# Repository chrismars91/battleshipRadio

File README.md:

https://www.instructables.com/BattLedRadio-the-LED-Radio-Battleship-SAMD21-Editi/

*** New board gerber below with better JTAG programming pads and a battery powered option. Updated BOM in the link. ***
https://www.pcbway.com/project/shareproject/rfm69_battleship_battery_7544f334.html

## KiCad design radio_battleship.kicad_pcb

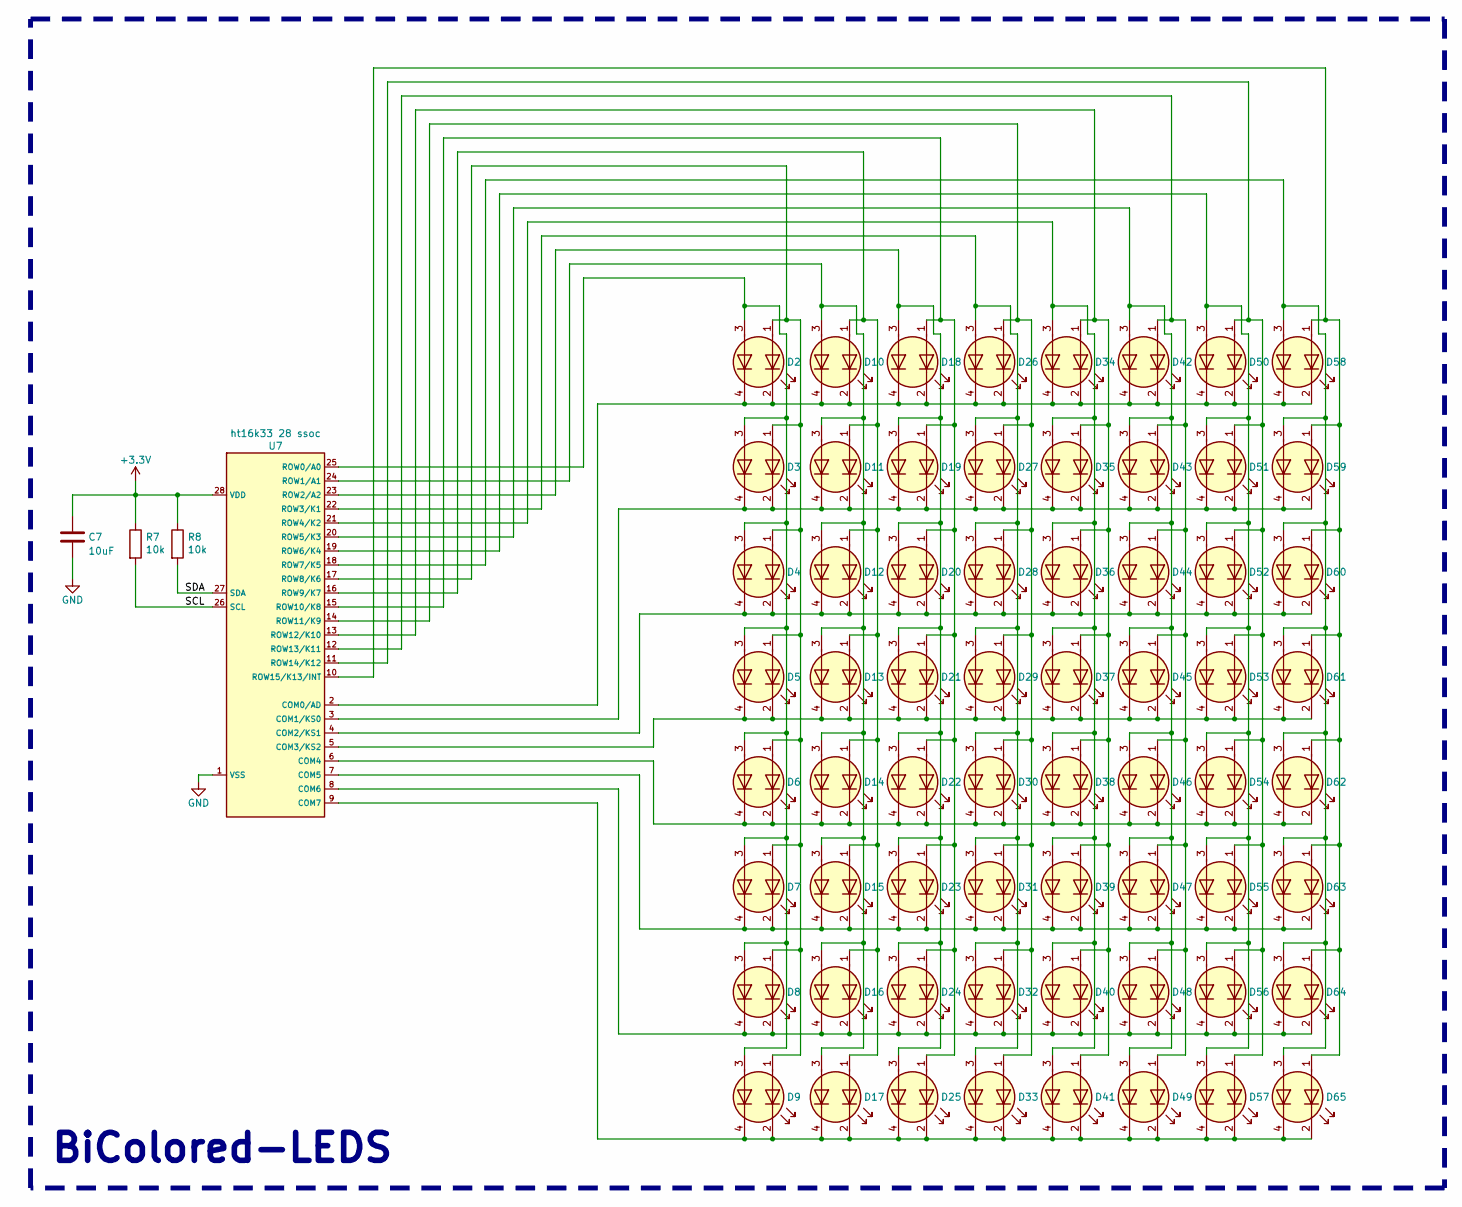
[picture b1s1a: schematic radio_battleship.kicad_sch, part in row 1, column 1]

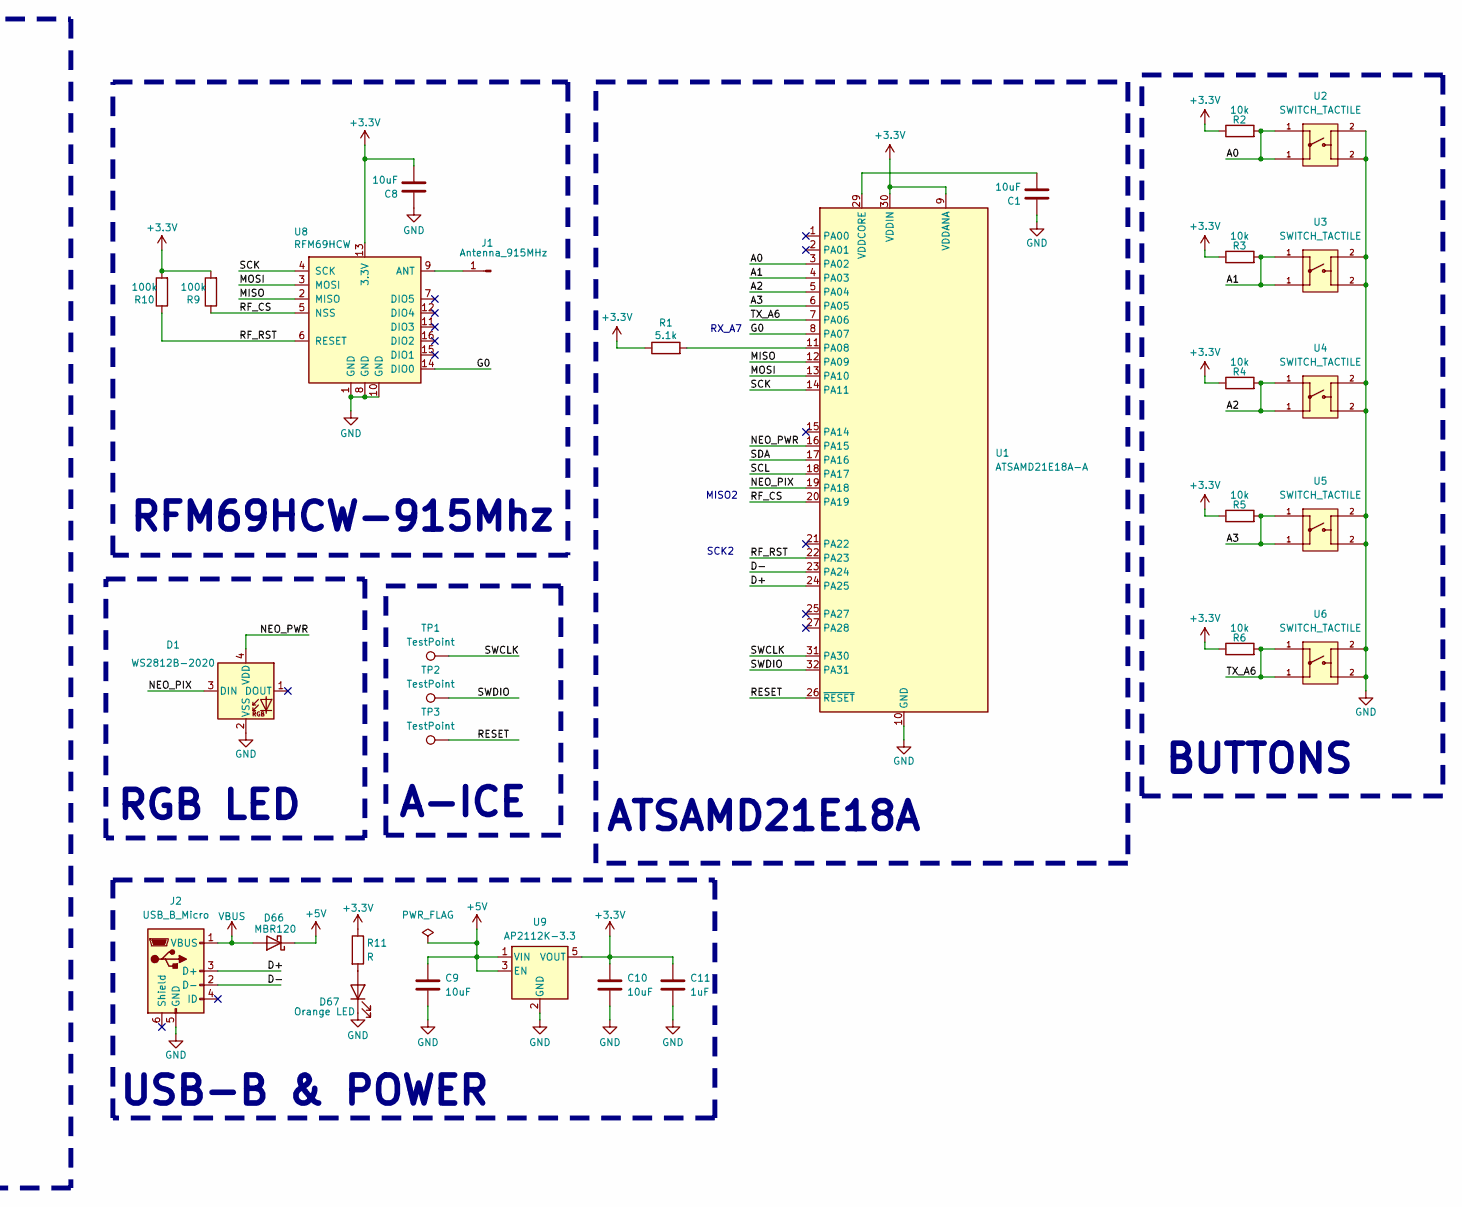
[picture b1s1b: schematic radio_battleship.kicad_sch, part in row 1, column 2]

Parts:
C1, C7, C8, C9, C10: 10uF; C_0603_1608Metric
C11: 1uF; C_0603_1608Metric
D1: WS2812B-2020; custom_ws28_2m_led
D2, D3, D4, D5, D6, D7, D8, D9, D10, D11, D12, D13, D14, D15, D16, D17, D18, D19, D20, D21, D22, D23, D24, D25, D26, D27, D28, D29, D30, D31, D32, D33, D34, D35, D36, D37, D38, D39, D40, D41, D42, D43, D44, D45, D46, D47, D48, D49, D50, D51, D52, D53, D54, D55, D56, D57, D58, D59, D60, D61, D62, D63, D64, D65: LTST-BILED-15X16
D66: MBR120; D_SOD-123F
D67: Orange LED; LED_0805_2012Metric
J1: Antenna_915MHz; ant
J2: USB_B_Micro; USB_Micro-B_Wuerth_629105150521
R1: 5.1k; R_0603_1608Metric
R2, R3, R4, R5, R6, R7, R8: 10k; R_0603_1608Metric
R9, R10: 100k; R_0603_1608Metric
R11: R; R_0603_1608Metric
TP1, TP2, TP3: TestPoint; TestPoint_Pad_2.5x2.5mm
U1: ATSAMD21E18A-A; TQFP-32_7x7mm_P0.8mm
U2, U3, U4, U5, U6: SWITCH_TACTILE
U7: ht16k33 28 ssoc; HT16K33_ssop
U8: RFM69HCW
U9: AP2112K-3.3; SOT-23-5

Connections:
+3.3V: C7.1, C8.2, C10.1, C11.1, R1.1, R2.1, R3.1, R4.1, R5.1, R6.1, R7.1, R8.1, R9.2, R10.2, R11.1, U1.9 (VDDANA), U1.30 (VDDIN), U7.28 (VDD), U8.13 (3.3V), U9.5 (VOUT)
+5V: C9.1, D66.1 (K), U9.1 (VIN), U9.3 (EN)
/A0: R2.2, U1.3 (PA02), U2.1
/A1: R3.2, U1.4 (PA03), U3.1
/A2: R4.2, U1.5 (PA04), U4.1
/A3: R5.2, U1.6 (PA05), U5.1
/D+: J2.3 (D+), U1.24 (PA25)
/D-: J2.2 (D-), U1.23 (PA24)
/G0: U1.8 (PA07), U8.14 (DIO0)
/MISO: U1.12 (PA09), U8.2 (MISO)
/MOSI: U1.13 (PA10), U8.3 (MOSI)
/NEO_PIX: D1.3 (DIN), U1.19 (PA18)
/NEO_PWR: D1.4 (VDD), U1.16 (PA15)
/RESET: TP3.1, U1.26 (~RESET)
/RF_CS: R9.1, U1.20 (PA19), U8.5 (NSS)
/RF_RST: R10.1, U1.22 (PA23), U8.6 (RESET)
/SCK: U1.14 (PA11), U8.4 (SCK)
/SCL: R7.2, U1.18 (PA17), U7.26 (SCL)
/SDA: R8.2, U1.17 (PA16), U7.27 (SDA)
/SWCLK: TP1.1, U1.31 (PA30)
/SWDIO: TP2.1, U1.32 (PA31)
/TX_A6: R6.2, U1.7 (PA06), U6.1
GND: C1.1, C7.2, C8.1, C9.2, C10.2, C11.2, D1.2 (VSS), D67.1 (K), J2.5 (GND), U1.10 (GND), U1.28 (GND), U2.2, U3.2, U4.2, U5.2, U6.2, U7.1 (VSS), U8.1 (GND), U8.8 (GND), U8.10 (GND), U9.2 (GND)
unnamed: D2.1 (A1), D3.1 (A1), D4.1 (A1), D5.1 (A1), D6.1 (A1), D7.1 (A1), D8.1 (A1), D9.1 (A1), U7.17 (ROW8/K6)
unnamed: D2.3 (A2), D3.3 (A2), D4.3 (A2), D5.3 (A2), D6.3 (A2), D7.3 (A2), D8.3 (A2), D9.3 (A2), U7.25 (ROW0/A0)
unnamed: D10.1 (A1), D11.1 (A1), D12.1 (A1), D13.1 (A1), D14.1 (A1), D15.1 (A1), D16.1 (A1), D17.1 (A1), U7.16 (ROW9/K7)
unnamed: D10.3 (A2), D11.3 (A2), D12.3 (A2), D13.3 (A2), D14.3 (A2), D15.3 (A2), D16.3 (A2), D17.3 (A2), U7.24 (ROW1/A1)
unnamed: D2.2 (K1), D2.4 (K2), D10.2 (K1), D10.4 (K2), D18.2 (K1), D18.4 (K2), D26.2 (K1), D26.4 (K2), D34.2 (K1), D34.4 (K2), D42.2 (K1), D42.4 (K2), D50.2 (K1), D50.4 (K2), D58.2 (K1), D58.4 (K2), U7.2 (COM0/AD)
unnamed: D3.2 (K1), D3.4 (K2), D11.2 (K1), D11.4 (K2), D19.2 (K1), D19.4 (K2), D27.2 (K1), D27.4 (K2), D35.2 (K1), D35.4 (K2), D43.2 (K1), D43.4 (K2), D51.2 (K1), D51.4 (K2), D59.2 (K1), D59.4 (K2), U7.3 (COM1/KS0)
unnamed: D4.2 (K1), D4.4 (K2), D12.2 (K1), D12.4 (K2), D20.2 (K1), D20.4 (K2), D28.2 (K1), D28.4 (K2), D36.2 (K1), D36.4 (K2), D44.2 (K1), D44.4 (K2), D52.2 (K1), D52.4 (K2), D60.2 (K1), D60.4 (K2), U7.4 (COM2/KS1)
unnamed: D5.2 (K1), D5.4 (K2), D13.2 (K1), D13.4 (K2), D21.2 (K1), D21.4 (K2), D29.2 (K1), D29.4 (K2), D37.2 (K1), D37.4 (K2), D45.2 (K1), D45.4 (K2), D53.2 (K1), D53.4 (K2), D61.2 (K1), D61.4 (K2), U7.5 (COM3/KS2)
unnamed: D6.2 (K1), D6.4 (K2), D14.2 (K1), D14.4 (K2), D22.2 (K1), D22.4 (K2), D30.2 (K1), D30.4 (K2), D38.2 (K1), D38.4 (K2), D46.2 (K1), D46.4 (K2), D54.2 (K1), D54.4 (K2), D62.2 (K1), D62.4 (K2), U7.6 (COM4)
unnamed: D7.2 (K1), D7.4 (K2), D15.2 (K1), D15.4 (K2), D23.2 (K1), D23.4 (K2), D31.2 (K1), D31.4 (K2), D39.2 (K1), D39.4 (K2), D47.2 (K1), D47.4 (K2), D55.2 (K1), D55.4 (K2), D63.2 (K1), D63.4 (K2), U7.7 (COM5)
unnamed: D8.2 (K1), D8.4 (K2), D16.2 (K1), D16.4 (K2), D24.2 (K1), D24.4 (K2), D32.2 (K1), D32.4 (K2), D40.2 (K1), D40.4 (K2), D48.2 (K1), D48.4 (K2), D56.2 (K1), D56.4 (K2), D64.2 (K1), D64.4 (K2), U7.8 (COM6)
unnamed: D9.2 (K1), D9.4 (K2), D17.2 (K1), D17.4 (K2), D25.2 (K1), D25.4 (K2), D33.2 (K1), D33.4 (K2), D41.2 (K1), D41.4 (K2), D49.2 (K1), D49.4 (K2), D57.2 (K1), D57.4 (K2), D65.2 (K1), D65.4 (K2), U7.9 (COM7)
unnamed: D18.1 (A1), D19.1 (A1), D20.1 (A1), D21.1 (A1), D22.1 (A1), D23.1 (A1), D24.1 (A1), D25.1 (A1), U7.15 (ROW10/K8)
unnamed: D18.3 (A2), D19.3 (A2), D20.3 (A2), D21.3 (A2), D22.3 (A2), D23.3 (A2), D24.3 (A2), D25.3 (A2), U7.23 (ROW2/A2)
unnamed: D26.1 (A1), D27.1 (A1), D28.1 (A1), D29.1 (A1), D30.1 (A1), D31.1 (A1), D32.1 (A1), D33.1 (A1), U7.14 (ROW11/K9)
unnamed: D26.3 (A2), D27.3 (A2), D28.3 (A2), D29.3 (A2), D30.3 (A2), D31.3 (A2), D32.3 (A2), D33.3 (A2), U7.22 (ROW3/K1)
unnamed: D34.1 (A1), D35.1 (A1), D36.1 (A1), D37.1 (A1), D38.1 (A1), D39.1 (A1), D40.1 (A1), D41.1 (A1), U7.13 (ROW12/K10)
unnamed: D34.3 (A2), D35.3 (A2), D36.3 (A2), D37.3 (A2), D38.3 (A2), D39.3 (A2), D40.3 (A2), D41.3 (A2), U7.21 (ROW4/K2)
unnamed: D42.1 (A1), D43.1 (A1), D44.1 (A1), D45.1 (A1), D46.1 (A1), D47.1 (A1), D48.1 (A1), D49.1 (A1), U7.12 (ROW13/K11)
unnamed: D42.3 (A2), D43.3 (A2), D44.3 (A2), D45.3 (A2), D46.3 (A2), D47.3 (A2), D48.3 (A2), D49.3 (A2), U7.20 (ROW5/K3)
unnamed: D50.1 (A1), D51.1 (A1), D52.1 (A1), D53.1 (A1), D54.1 (A1), D55.1 (A1), D56.1 (A1), D57.1 (A1), U7.11 (ROW14/K12)
unnamed: D50.3 (A2), D51.3 (A2), D52.3 (A2), D53.3 (A2), D54.3 (A2), D55.3 (A2), D56.3 (A2), D57.3 (A2), U7.19 (ROW6/K4)
unnamed: D58.1 (A1), D59.1 (A1), D60.1 (A1), D61.1 (A1), D62.1 (A1), D63.1 (A1), D64.1 (A1), D65.1 (A1), U7.10 (ROW15/K13/INT)
unnamed: D58.3 (A2), D59.3 (A2), D60.3 (A2), D61.3 (A2), D62.3 (A2), D63.3 (A2), D64.3 (A2), D65.3 (A2), U7.18 (ROW7/K5)
unnamed: D67.2 (A), R11.2
unnamed: J1.1, U8.9 (ANT)
unnamed: R1.2, U1.11 (PA08)
unnamed: C1.2, U1.29 (VDDCORE)
VBUS: D66.2 (A), J2.1 (VBUS)

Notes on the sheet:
ATSAMD21E18A
RX_A7
RGB LED
MISO2
USB-B & POWER
SCK2
BiColored-LEDS
BUTTONS
A-ICE
RFM69HCW-915Mhz

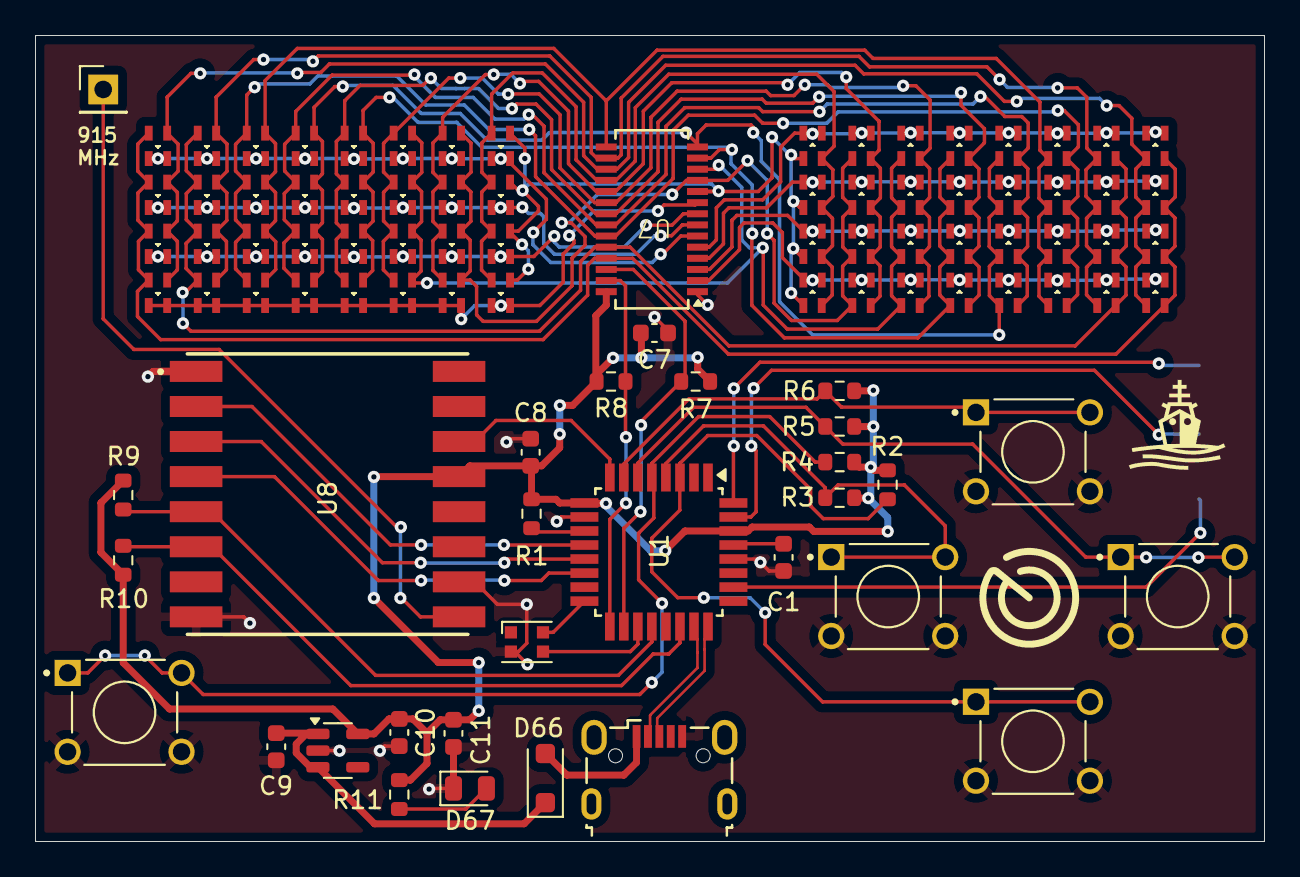
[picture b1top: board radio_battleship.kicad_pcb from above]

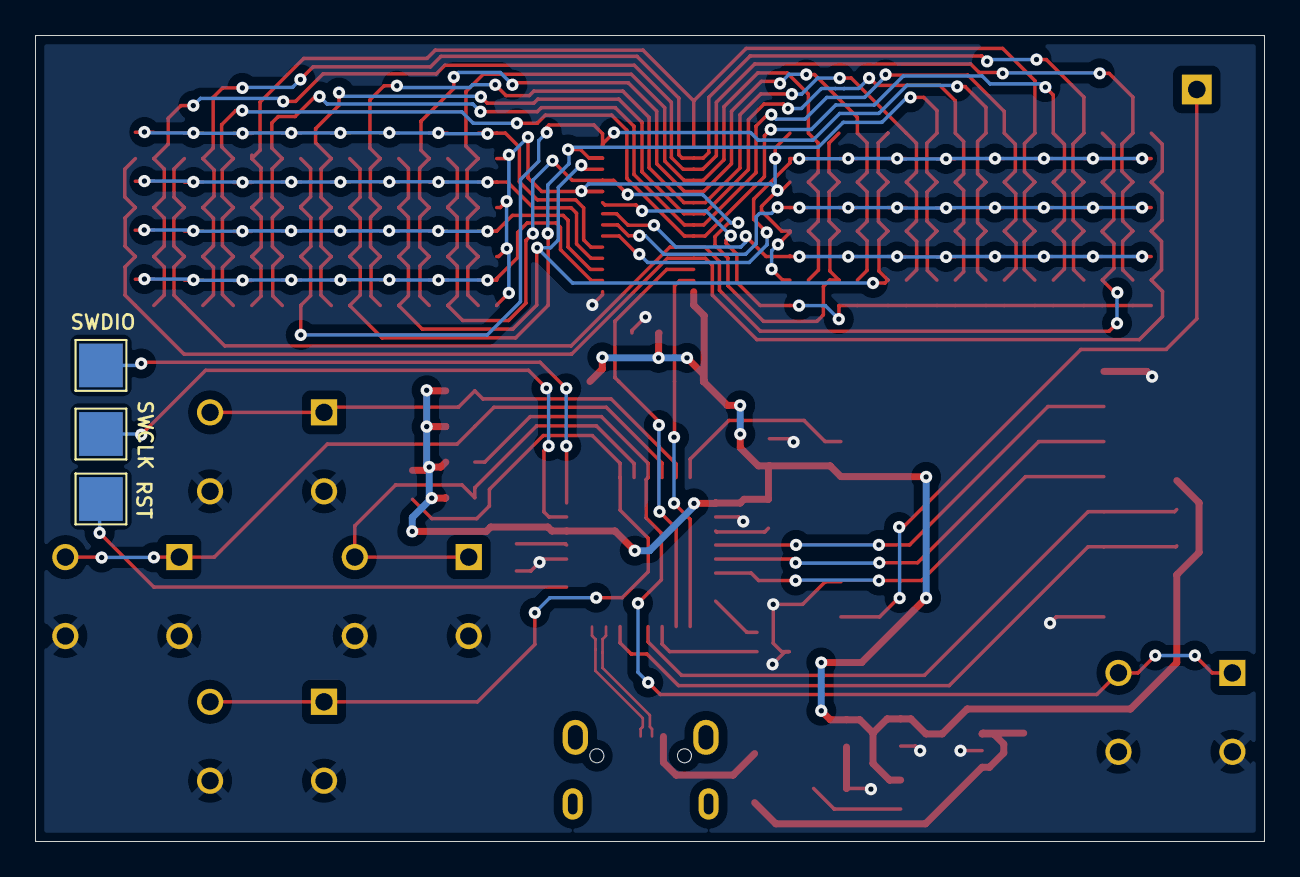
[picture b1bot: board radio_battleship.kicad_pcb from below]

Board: 2 copper layers, 70.1 x 46.0 mm, 98 parts (3 on the bottom side), 52 nets.
